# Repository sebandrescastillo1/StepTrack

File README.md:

# StepTrack - Contador de pasos en escalera
Repositorio contador de pasos 
## Contenido
- Librerias_eagle: Contiene librería de componentes de EAGLE utilizados para el contador de pasos.
- Documentos: Contiene los informes entregables de ELO301
- Datasheets: Contiene los datasheets de los componentes y otros documentos de interés.
- Entregable_PCB: Archivos entregables para PCB - COM & XLSX
- StepTruck_Esquematico.csv: BOM de EAGLE
- StepTruck_Esquematico.pdf: Esquemático EAGLE en formato pdf
- StepTruck_Esquematico.sch: ESquemático EAGLE en formato sch
- StepTruck_Esquematico.brd: Diseño PCB EAGLE en formato brd

## Autores
Grupo 2 - ELO301 S2 2023
- Paula Cartagena
- Sebastian Castillo
- Sebastian Madariaga
- Juan Piñeiro

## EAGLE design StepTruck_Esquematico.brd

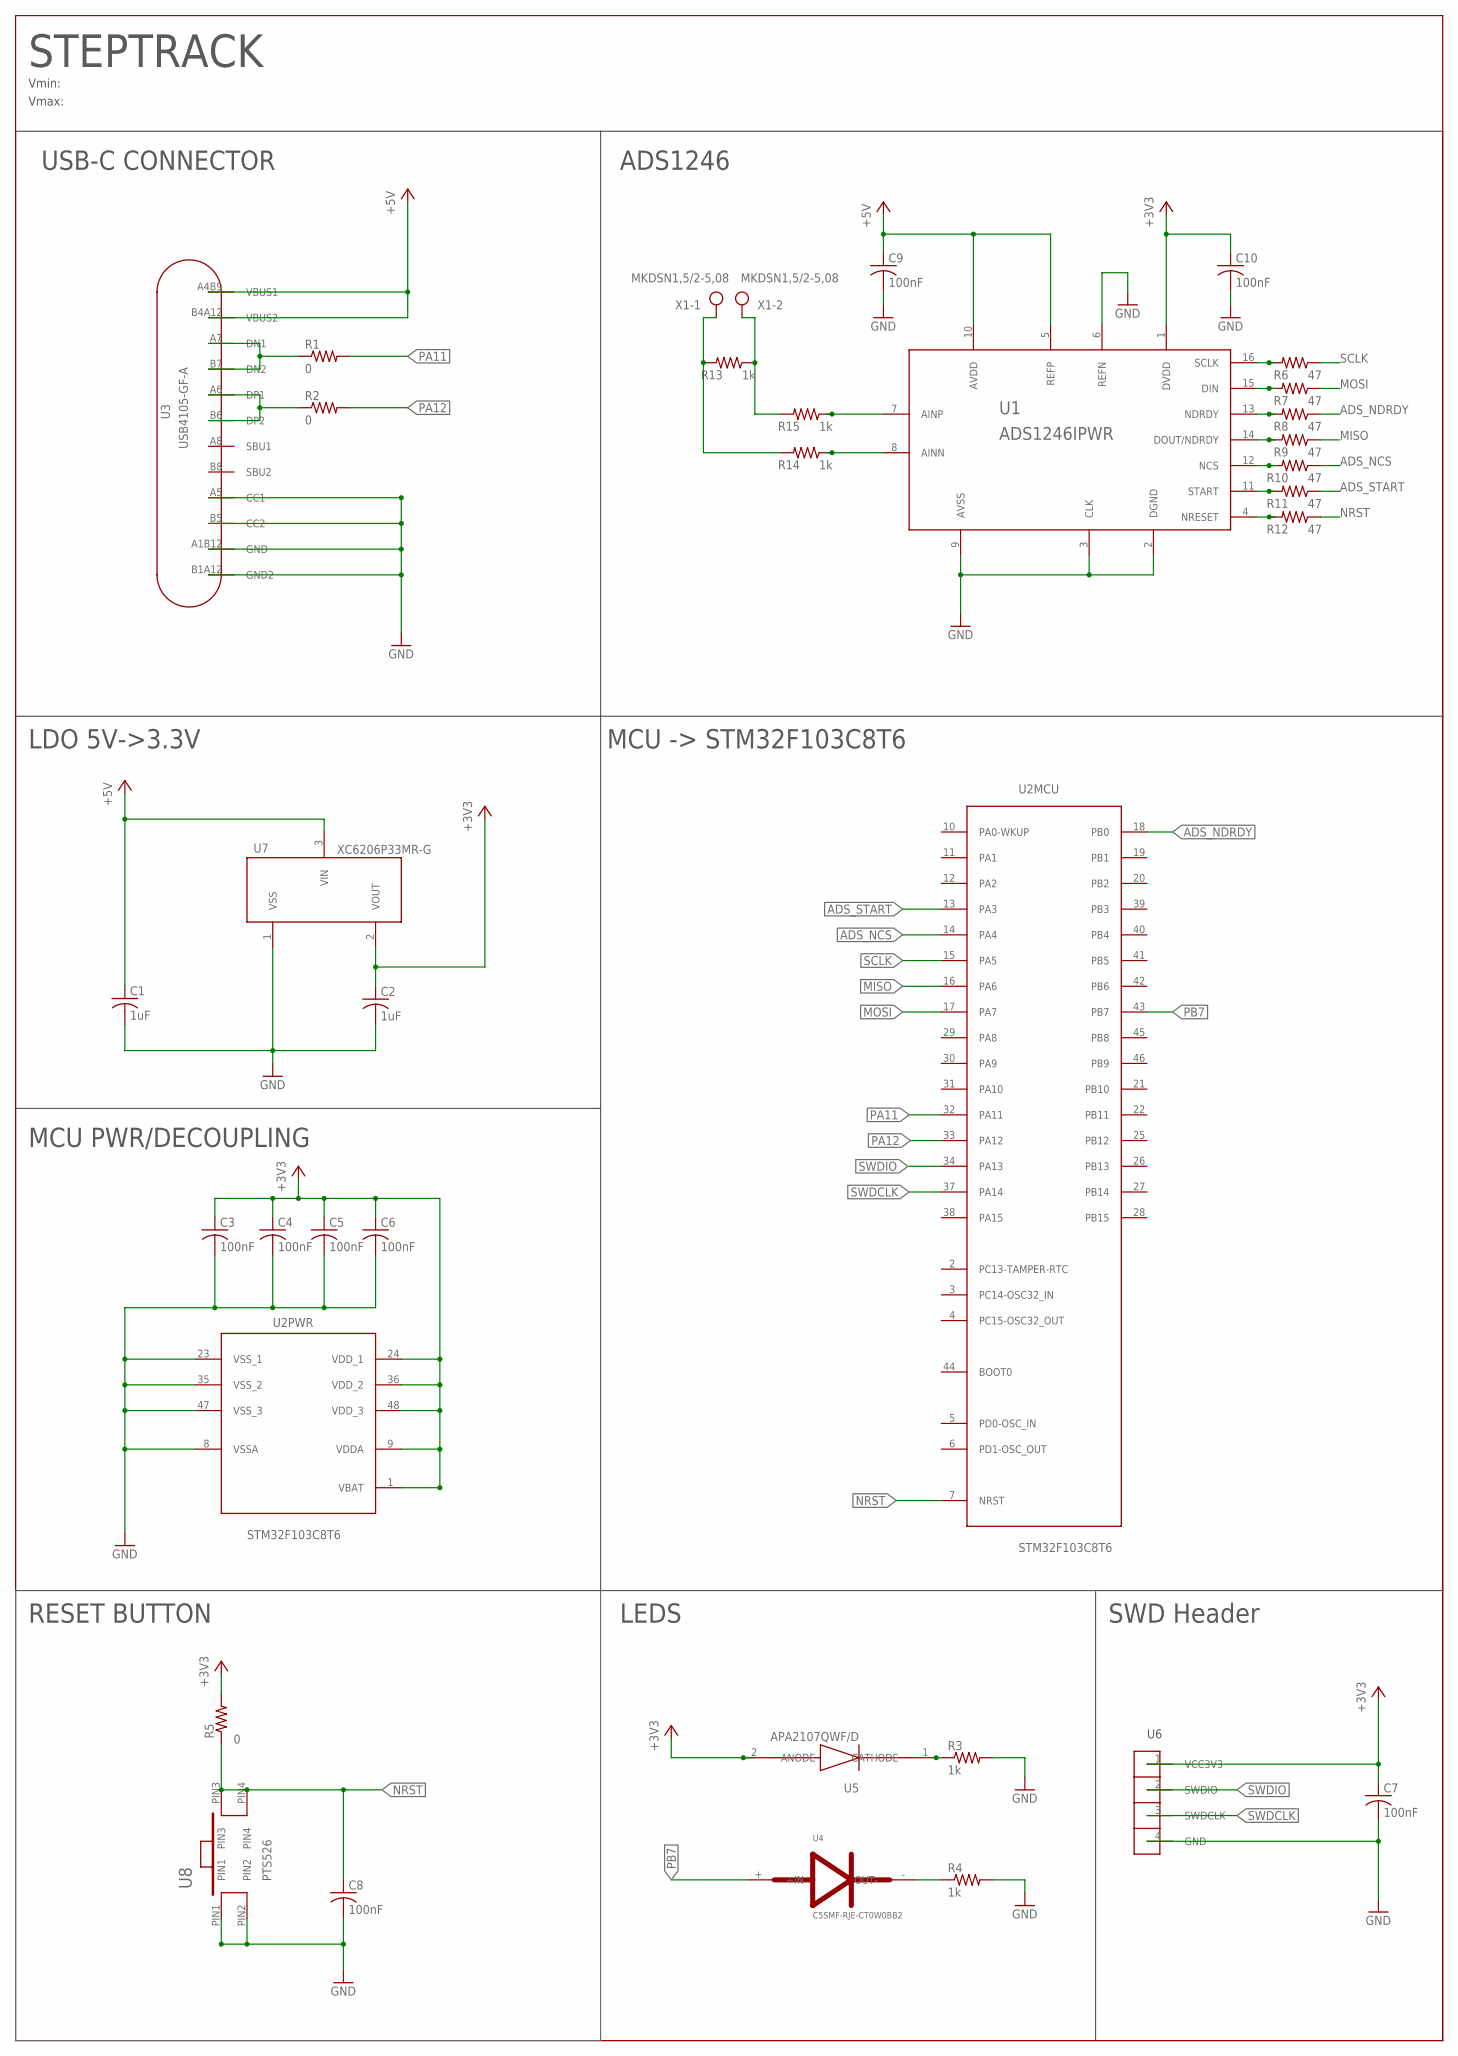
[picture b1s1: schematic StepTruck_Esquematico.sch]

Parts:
C1, C2: 1uF; C0805K
C3, C4, C5, C6, C7, C8, C9, C10: 100nF; C0805K
R1, R2, R5: 0; R0805
R3, R4, R13, R14, R15: 1k; R0805
R6, R7, R8, R9, R10, R11, R12: 47; R0805
U1: ADS1246IPWR
U2: STM32F103C8T6; 48-LQFP
U3: USB4105-GF-A
U4: C5SMF-RJE-CT0W0BB2
U5: APA2107QWF/D
U6: TS104TAA; TS-104-T-AA
U7: XC6206P33MR-G; SOT-23
U8: PTS526
X1: MKDSN1,5/2-5,08

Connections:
+3V3: C2.1, C3.1, C4.1, C5.1, C6.1, C7.1, C10.1, R5.2, U1.1 (DVDD), U2.1 (VBAT), U2.9 (VDDA), U2.24 (VDD_1), U2.36 (VDD_2), U2.48 (VDD_3), U5.2 (ANODE), U6.1 (VCC3V3), U7.2 (VOUT)
+5V: C1.1, C9.1, U1.5 (REFP), U1.10 (AVDD), U3.A4B9 (VBUS1), U3.B4A12 (VBUS2), U7.3 (VIN)
ADS_NCS: R10.1, U2.14 (PA4)
ADS_NDRDY: R8.1, U2.18 (PB0)
ADS_START: R11.1, U2.13 (PA3)
GND: C1.2, C2.2, C3.2, C4.2, C5.2, C6.2, C7.2, C8.2, C9.2, C10.2, R3.2, R4.2, U1.2 (DGND), U1.3 (CLK), U1.6 (REFN), U1.9 (AVSS), U2.8 (VSSA), U2.23 (VSS_1), U2.35 (VSS_2), U2.47 (VSS_3), U3.A1B12 (GND), U3.A5 (CC1), U3.B1A12 (GND2), U3.B5 (CC2), U6.4 (GND), U7.1 (VSS), U8.PIN1, U8.PIN2
MISO: R9.1, U2.16 (PA6)
MOSI: R7.1, U2.17 (PA7)
unnamed: R1.1, U3.A7 (DN1), U3.B7 (DN2)
unnamed: R15.1, U1.7 (AINP)
unnamed: R2.1, U3.A6 (DP1), U3.B6 (DP2)
unnamed: R14.1, U1.8 (AINN)
unnamed: R3.1, U5.1 (CATHODE)
unnamed: R4.1, U4.- (OUT-)
unnamed: R12.2, U1.4 (NRESET)
unnamed: R11.2, U1.11 (START)
unnamed: R10.2, U1.12 (NCS)
unnamed: R9.2, U1.14 (DOUT/NDRDY)
unnamed: R8.2, U1.13 (NDRDY)
unnamed: R7.2, U1.15 (DIN)
unnamed: R6.2, U1.16 (SCLK)
unnamed: R13.2, R14.2, X1.1
unnamed: R13.1, R15.2, X1.2
NRST: C8.1, R5.1, R12.1, U2.7 (NRST), U8.PIN3, U8.PIN4
PA11: R1.2, U2.32 (PA11)
PA12: R2.2, U2.33 (PA12)
PB7: U2.43 (PB7), U4.+ (+IN)
SCLK: R6.1, U2.15 (PA5)
SWDCLK: U2.37 (PA14), U6.3 (SWDCLK)
SWDIO: U2.34 (PA13), U6.2 (SWDIO)

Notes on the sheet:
STEPTRACK
USB-C CONNECTOR
ADS1246
MCU -> STM32F103C8T6
LDO 5V->3.3V
MCU PWR/DECOUPLING
RESET BUTTON
SWD Header
LEDS
Vmin:
Vmax:

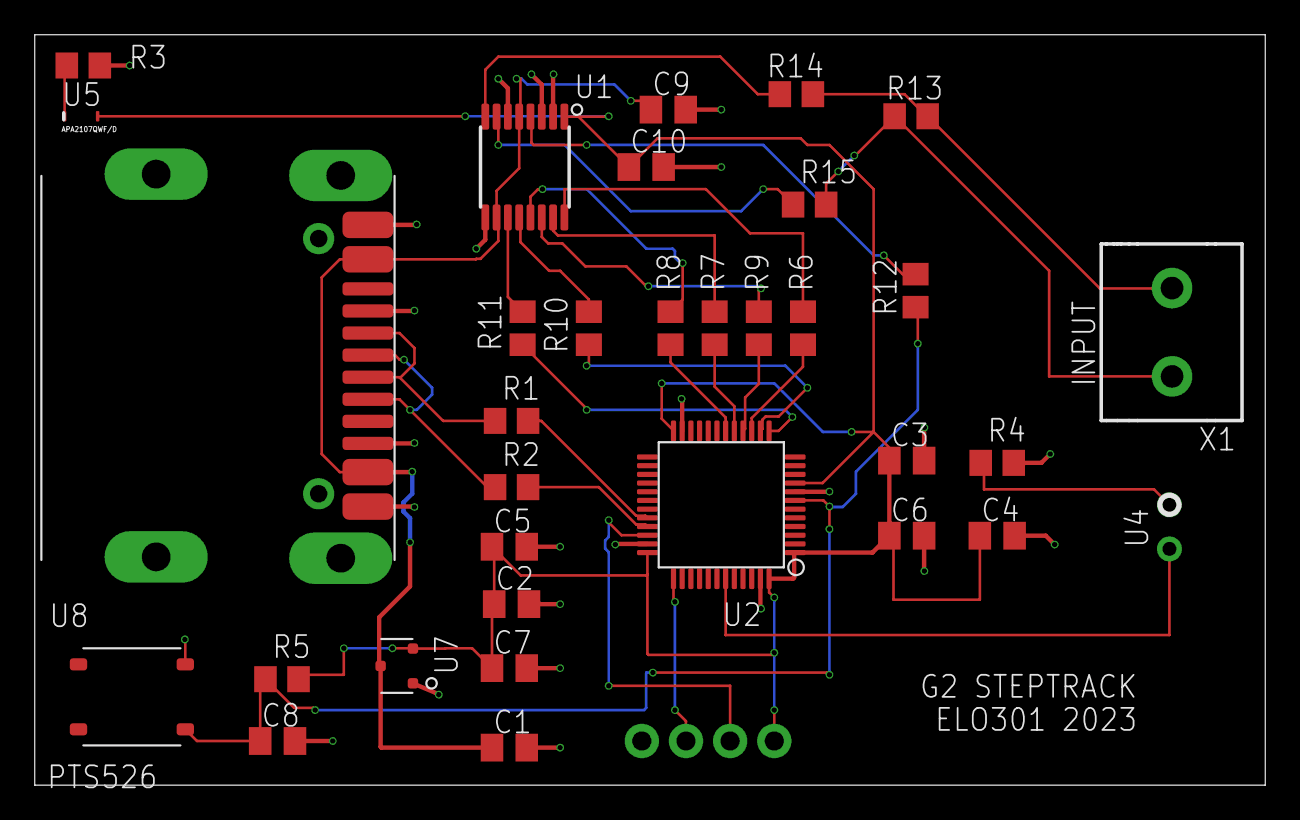
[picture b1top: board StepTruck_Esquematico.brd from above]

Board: 2 copper layers, 70.8 x 43.2 mm, 34 parts (0 on the bottom side), 30 nets.

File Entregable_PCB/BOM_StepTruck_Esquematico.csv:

"Qty";"Value";"Device";"Package";"Parts";"Description";"POPULARITY";"SPICEPREFIX";
"3";"0";"R-US_R0805";"R0805";"R1, R2, R5";"RESISTOR, American symbol";"85";"R";
"8";"100nF";"C-USC0805K";"C0805K";"C3, C4, C5, C6, C7, C8, C9, C10";"CAPACITOR, American symbol";"19";"C";
"5";"1k";"R-US_R0805";"R0805";"R3, R4, R13, R14, R15";"RESISTOR, American symbol";"85";"R";
"2";"1uF";"C-USC0805K";"C0805K";"C1, C2";"CAPACITOR, American symbol";"19";"C";
"7";"47";"R-US_R0805";"R0805";"R6, R7, R8, R9, R10, R11, R12";"RESISTOR, American symbol";"85";"R";
"1";"ADS1246IPWR";"ADS1246IPWR";"ADS1246IPWR";"U1";"";"";"";
"1";"APA2107QWF/D";"APA2107QWF/D";"APA2107QWF/D";"U5";"";"";"";
"1";"C5SMF-RJE-CT0W0BB2";"C5SMF-RJE-CT0W0BB2";"C5SMF-RJE-CT0W0BB2";"U4";"";"";"";
"1";"MKDSN1,5/2-5,08";"MKDSN1,5/2-5,08";"MKDSN1,5/2-5,08";"X1";"MKDSN 1,5/ 2-5,08 Printklemme";"14";"";
"1";"PTS526";"PTS526";"PTS526";"U8";"";"";"";
"1";"STM32F103C8T6";"STM32F103C8T6";"48-LQFP";"U2";"";"";"";
"1";"TS104TAA";"TS104TAA";"TS-104-T-AA";"U6";"";"";"";
"1";"USB4105-GF-A";"USB4105-GF-A";"USB4105-GF-A";"U3";"";"";"";
"1";"XC6206P33MR-G";"XC6206P33MR-G";"SOT-23";"U7";"";"";"";

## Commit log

2023-10-18 Se sube contenido de eagle para STM32F103C8T6
2023-10-18 Se sube contenido de STM32F103C8T6
2023-10-18 Orden STM32
2023-10-18 Se agrega STM32 y LDO
2023-10-18 RE ORDEN LIBRERIA
2023-10-19 ENTREGA_V1
2023-10-19 Nuevas versiones V2
2023-10-28 Se agregan documentos anteriores + cambio de nombres
2023-10-29 Add files via upload
    Se agrega librería con conector USB C
2023-10-29 Actualizacion STM32
    Se arregla esquematico
2023-10-29 Add files via upload
    se coloca el part number al ADS
2023-10-29 se coloca part number
2023-10-29 se pone part number
2023-10-29 part number
2023-10-29 pnumber
2023-10-29 Rename led_blanco.lbr to LED_BLANCO.lbr
2023-10-29 Rename led_rojo.lbr to LED_ROJO.lbr
2023-10-29 Header SWD
2023-10-29 Cambio Conector USB
    Se elimina del dispositivo PD Controller
2023-10-30 Se agregan datasheets
2023-10-30 Esquematico StepTrack
    Se sube esquemático modificado, con las mejoras propuestas y con terminaciones pulidas.
2023-10-30 Librerías de componentes actualizadas
    Se resuben los componentes modificados.
2023-10-30 Actualizacion Esquematico
2023-10-30 Se actualizan archivos para esquematico
2023-10-31 Pcb_v1
2023-10-31 Entregable PCB
2023-10-31 Documento de Diseño Actualizado
